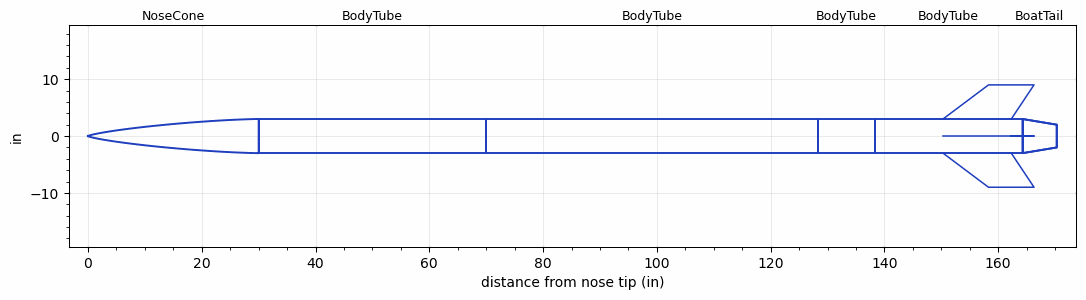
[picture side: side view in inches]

<RASAeroDocument>
 <FileVersion>2</FileVersion>
 <RocketDesign>
  <NoseCone>
   <Length>29.9999</Length>
   <Diameter>6</Diameter>
   <Shape>Von Karman Ogive</Shape>
   <Location>0</Location>
  </NoseCone>
  <BodyTube>
   <Length>39.9999</Length>
   <Diameter>6</Diameter>
   <Location>29.9999</Location>
  </BodyTube>
  <BodyTube>
   <Length>58.2999</Length>
   <Diameter>6</Diameter>
   <Location>69.9999</Location>
  </BodyTube>
  <BodyTube>
   <Length>10</Length>
   <Diameter>6</Diameter>
   <Location>128.2997</Location>
  </BodyTube>
  <BodyTube>
   <Length>25.9999</Length>
   <Diameter>6</Diameter>
   <Location>138.2997</Location>
   <BoattailLength>6</BoattailLength>
   <BoattailRearDiameter>4</BoattailRearDiameter>
   <Fin>
    <Count>4</Count>
    <Chord>12</Chord>
    <Span>6</Span>
    <SweepDistance>8</SweepDistance>
    <TipChord>8</TipChord>
    <Thickness>0.3</Thickness>
    <Location>14</Location>
    <AirfoilSection>Square</AirfoilSection>
   </Fin>
  </BodyTube>
  <BoatTail>
   <Length>6</Length>
   <Diameter>6</Diameter>
   <RearDiameter>4</RearDiameter>
   <Location>164.2997</Location>
  </BoatTail>
  <Surface>Rough Camouflage Paint</Surface>
  <ModifiedBarrowman>True</ModifiedBarrowman>
  <Turbulence>False</Turbulence>
  <UseBooster1>False</UseBooster1>
  <UseBooster2>False</UseBooster2>
 </RocketDesign>
 <LaunchSite>
  <Altitude>0</Altitude>
  <Pressure>29.9214</Pressure>
  <RodAngle>0</RodAngle>
  <RodLength>3.2808</RodLength>
  <Temperature>59</Temperature>
  <WindSpeed>4.4739</WindSpeed>
 </LaunchSite>
 <Recovery>
  <Altitude1>656.168</Altitude1>
  <Altitude2>656.168</Altitude2>
  <DeviceType1>Parachute</DeviceType1>
  <DeviceType2>Parachute</DeviceType2>
  <Event1>True</Event1>
  <Event2>True</Event2>
  <Size1>11.811</Size1>
  <Size2>11.811</Size2>
  <EventType1>Apogee</EventType1>
  <EventType2>Apogee</EventType2>
  <CD1>0.8</CD1>
  <CD2>0</CD2>
 </Recovery>
 <SimulationList>
  <Simulation>
   <SustainerLaunchWt>120.7535</SustainerLaunchWt>
   <SustainerCG>106.5272</SustainerCG>
   <SustainerIgnitionDelay>0</SustainerIgnitionDelay>
   <Booster1SeparationDelay>0</Booster1SeparationDelay>
   <Booster1IgnitionDelay>0</Booster1IgnitionDelay>
   <IncludeBooster1>False</IncludeBooster1>
   <Booster2Delay>0</Booster2Delay>
   <IncludeBooster2>False</IncludeBooster2>
  </Simulation>
 </SimulationList>
</RASAeroDocument>
